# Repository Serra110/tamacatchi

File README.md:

# Tamacatchi

Tamacatchi is a small virtual pet inspired by the original Tamagotchi, a handheld digital pet that you take care of by feeding it, playing with it and letting it rest. The idea behind this project is to create a physical device where you can interact with your pet using buttons and movement controls.

The device includes a screen to display the pet and its stats, a buzzer for sound feedback, an RTC to keep track of time, and a temperature and humidity sensor. It also uses an MPU6050, which lets you tilt the device to navigate the menu or shake it to make the pet react and change its stats. This is my first attempt at designing a complete project in KiCad, including both the schematic and PCB layout, so it has been a great learning experience.

## Hardware Design

### 3D Model

A 3D representation of the project designed in KiCad.

### Schematic

The schematic showing the circuit and component connections.

## Code

The code was updated to support the additional components introduced in the tutorial, including the RTC and the buzzer.

## Controls

- **Button 1 (D2):** Opens the radial menu or confirms a selection.
- **Button 2 (D3):** Switches between the pet view and stats view.
- **MPU6050:** Tilt the device to navigate the menu, or shake it to make the pet react and change stats.

### Menu Actions

- **Up:** Nap
- **Right:** Play
- **Down:** Feed
- **Left:** Pet

## About the Project

This is my first time designing a complete PCB in KiCad, from the schematic to the PCB layout. I still have things I would like to improve, especially the copper routing, since I mainly focused on getting everything connected rather than optimizing the layout. Overall, this project has helped me learn more about electronics, circuit design and PCB development, and I hope to improve it further in the future.

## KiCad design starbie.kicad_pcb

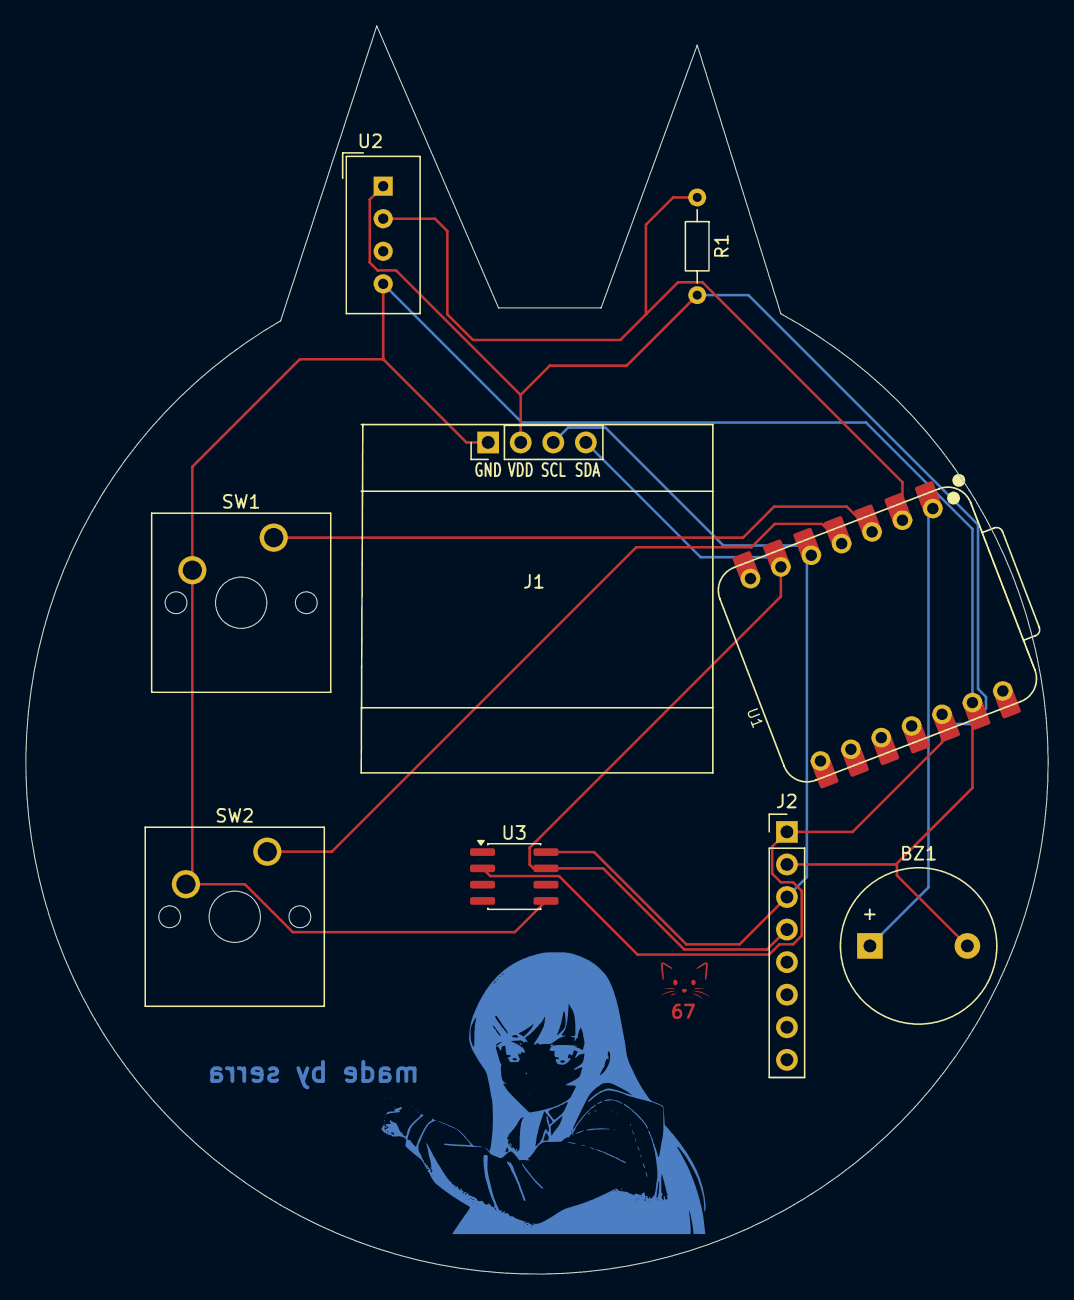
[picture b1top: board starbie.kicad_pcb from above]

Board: 2 copper layers, 79.7 x 97.4 mm, 9 parts (0 on the bottom side), 8 nets.

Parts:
BZ1: Buzzer; Buzzer_12x9.5RM7.6
J1: Conn_01x04_Pin; Display_128x64_096_I2C
J2: Conn_01x08_Pin; PinHeader_1x08_P2.54mm_Vertical
R1: 10k; R_Axial_DIN0204_L3.6mm_D1.6mm_P7.62mm_Horizontal
SW1, SW2: SW_Push; SW_Cherry_MX_1.00u_PCB
U1: XIAO-ESP32-C3-SMD; XIAO-ESP32-C6-DIP
U2: DHT11; Aosong_DHT11_5.5x12.0_P2.54mm
U3: DS3231MZ; SOIC-8_3.9x4.9mm_P1.27mm

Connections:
+3.3V: J1.2, J2.1, R1.2, U1.12 (3V3_OUT), U2.1 (VDD), U3.2 (VCC)
/DHT11 DATA: R1.1, U1.2 (D1), U2.2 (DATA)
/GPIO2: SW1.1, U1.3 (D2)
/GPIO3: SW2.1, U1.4 (D3)
/SCL: J1.3, J2.3, U1.5 (D4), U3.8 (SCL)
/SDA: J1.4, J2.4, U1.6 (D5), U3.7 (SDA)
GND: BZ1.2 (-), J1.1, J2.2, SW1.2, SW2.2, U1.13 (GND), U2.4 (GND), U3.5 (GND)
unnamed: BZ1.1 (+), U1.1 (D0)
